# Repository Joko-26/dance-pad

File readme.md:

## My first PCB ever!!

### A tiny reaction/speed figet toy based on the RP2040, with keyboard switches!!!

In short you have to press the corresponding button when an led lights up

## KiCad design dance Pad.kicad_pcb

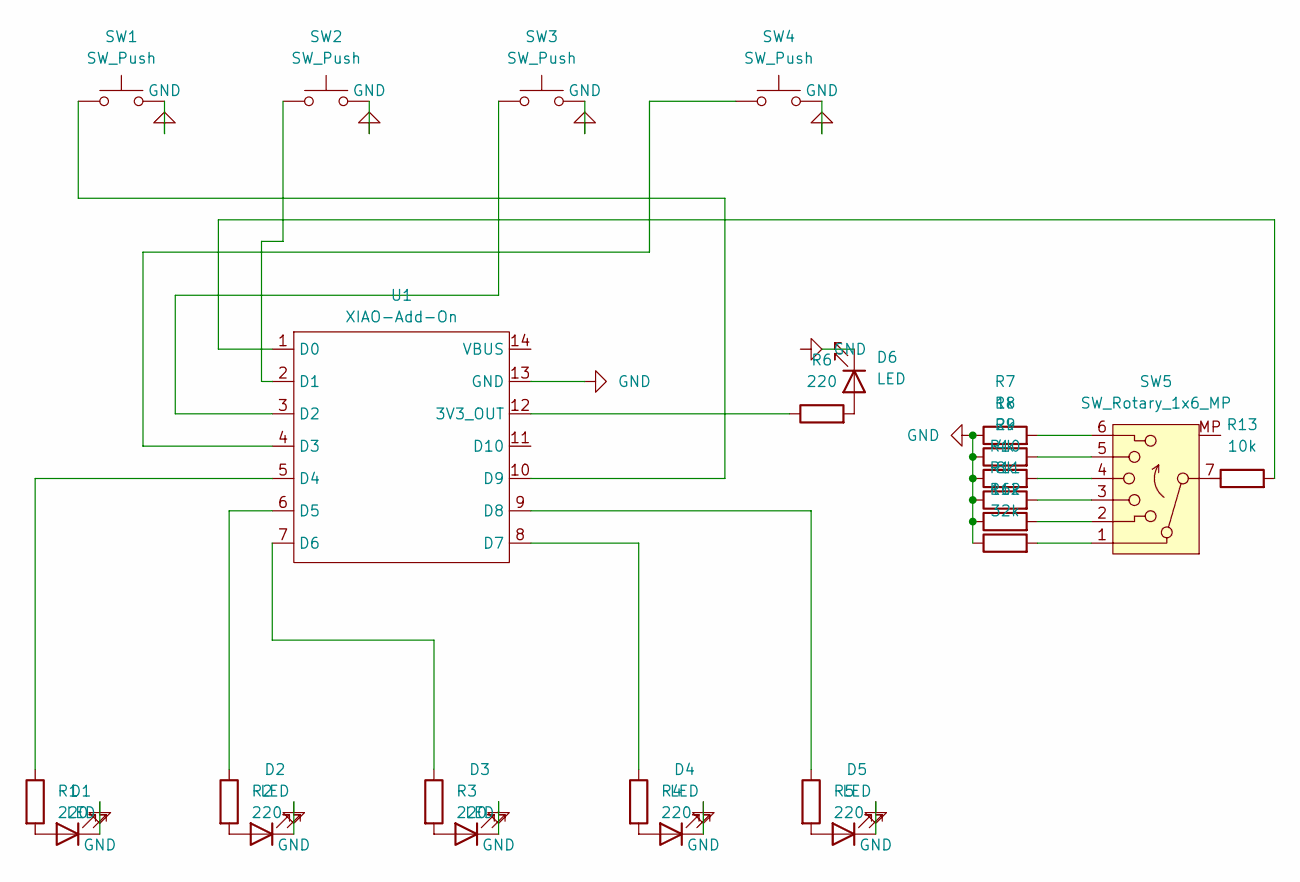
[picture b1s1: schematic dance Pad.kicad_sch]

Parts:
D1, D2, D3, D4, D5: LED; LED_D4.0mm
D6: LED; LED_0201_0603Metric
R1, R2, R3, R4, R5, R6: 220; R_01005_0402Metric
R7: 1k; R_01005_0402Metric
R8: 2k; R_01005_0402Metric
R9: 4k; R_01005_0402Metric
R10: 8k; R_01005_0402Metric
R11: 16k; R_01005_0402Metric
R12: 32k; R_01005_0402Metric
R13: 10k; R_01005_0402Metric
SW1, SW2, SW3, SW4: SW_Push; SW_Cherry_MX_1.00u_PCB
SW5: SW_Rotary_1x6_MP
U1: XIAO-Add-On; XIAO-RP2040-DIP

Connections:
GND: D1.1 (K), D2.1 (K), D3.1 (K), D4.1 (K), D5.1 (K), R7.1, R8.1, R9.1, R10.1, R11.1, R12.1, SW1.2, SW2.2, SW3.2, SW4.2, U1.13 (GND)
unnamed: D1.2 (A), R1.2
unnamed: D2.2 (A), R2.2
unnamed: D3.2 (A), R3.2
unnamed: D4.2 (A), R4.2
unnamed: D5.2 (A), R5.2
unnamed: D6.2 (A_2), R6.2
unnamed: R7.2, SW5.6
unnamed: R8.2, SW5.5
unnamed: R9.2, SW5.4
unnamed: R10.2, SW5.3
unnamed: R11.2, SW5.2
unnamed: R12.2, SW5.1
unnamed: R6.1, U1.12 (3V3_OUT)
unnamed: R13.2, U1.1 (D0)
unnamed: SW2.1, U1.2 (D1)
unnamed: SW3.1, U1.3 (D2)
unnamed: SW4.1, U1.4 (D3)
unnamed: R1.1, U1.5 (D4)
unnamed: R2.1, U1.6 (D5)
unnamed: R3.1, U1.7 (D6)
unnamed: R4.1, U1.8 (D7)
unnamed: R5.1, U1.9 (D8)
unnamed: SW1.1, U1.10 (D9)

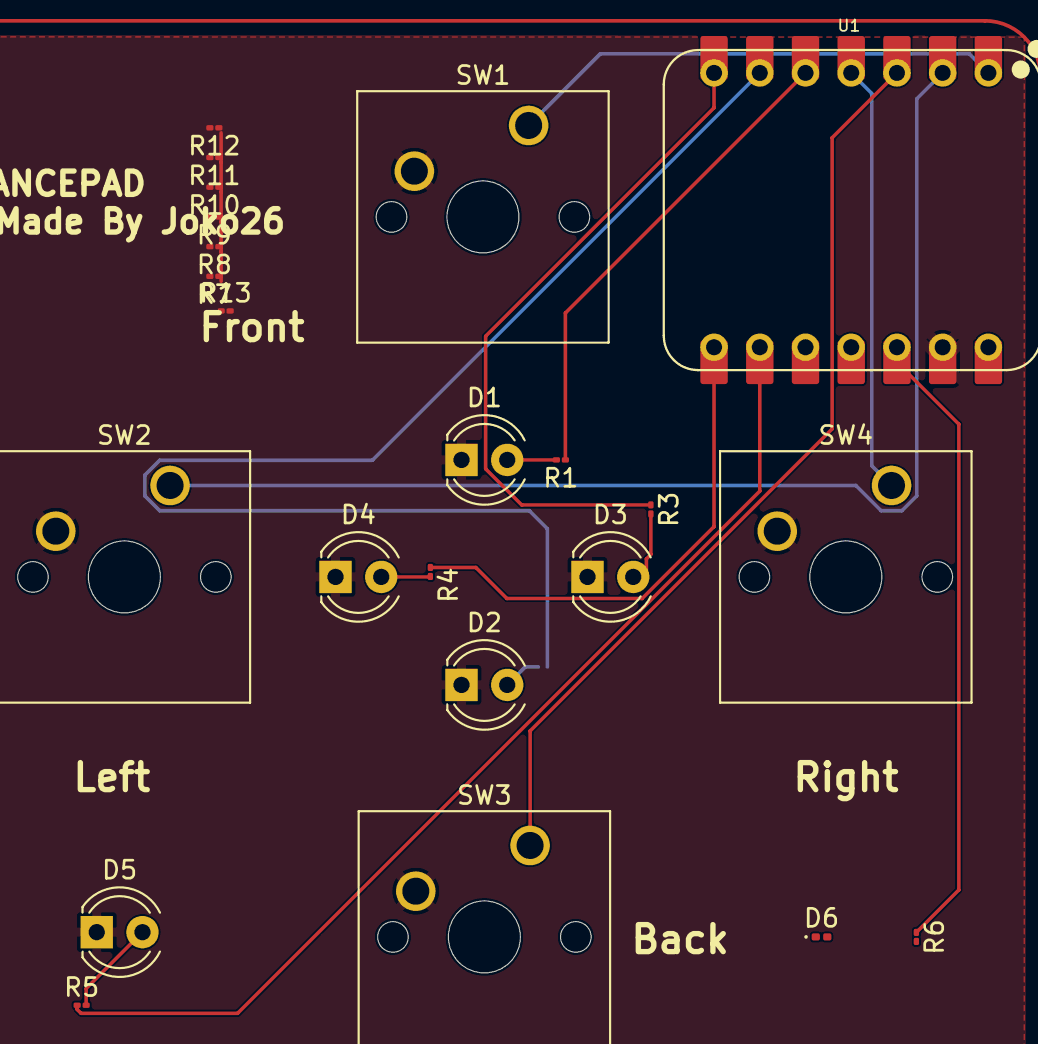
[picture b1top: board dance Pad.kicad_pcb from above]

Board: 2 copper layers, 24 parts (1 on the bottom side), 18 nets.
